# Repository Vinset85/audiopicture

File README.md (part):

# AudioPicture

Smart acoustic picture / complete Home Assistant room node.

**Product authority: [Rev.G frozen configuration](docs/architecture/v2.2-rev-g-clean.md).** 320 × 400 × 30 mm. Satellite1.1 Dev Kit and LD2450. One internal 24 V supply. Line-out to a stereo analog amplifier: XCITE XT19-4 on the left, Tectonic TEAX25C10-8/HS on the right. Volume is two taps on the bare bottom edge, left down and right up, with a latching microphone mute between them. Four LEDs sit under the cloth: white on header pin 1, blue on GPIO2 pin 13, red on GPIO14 pin 31, amber on GPIO18 pin 32. The 24-LED ring stays dark. The cloth drops into a front rabbet and finishes flush with the rim, held by fourteen magnets in that face. Frame: `mechanical/rev-g/cad/AP-G-FRAME.stl`. Digital checks: `evidence/rev-g/production-verification.json`. Not a production release.

**Supporting specs:** [DML panel](mechanical/dml-panel-rev-e.md), [electronics packaging](hardware/electronics-packaging-rev-e.md). Room logic already in `firmware/components/room_audio` and HA `room.py` carries forward; acoustic coefficients become DML-specific after measurement.

**Production package (digital):** [manufacturing/rev-e/](manufacturing/rev-e/) — gate register, BOM, OEM RFQ, assembly, factory test. CAD kernel STEP/STL in `mechanical/rev-e/cad/`. Modal screening in `evidence/rev-e/`. Mass production still requires OEM quotes, PCB fab, acoustic first article, product firmware on ESP-IDF, and certification (see gate register `OPEN_EXTERNAL`).

**Historical Rev.D (digital only, superseded):** [box model](mechanical/acoustic-box-model-rev-d.md) and [Rev.D architecture](docs/architecture/v2.2-rev-d-mono-room.md) for the 84 mm cone path.

**Historical structural checkpoint: [Rev.FI](mechanical/digital-validation-rev-fi.md).** It does not govern the radiator, the exciter, or the rear cavity. One serial refined-mesh weak-Y LC4 run passes the corner displacement check at 0.875290 mm and retains at least 0.173090 mm conservative final DML separation. The two-mesh displacement difference is 0.626581%; stress convergence remains OPEN. Weak-Z LC4 still fails. Materials, actual joints and complete product qualification remain OPEN. The 250 g frame ceiling remains removed.

The [Rev.FI supplement](https://github.com/Vinset85/audiopicture/releases/tag/checkpoint-rev-fi-2026-10-16) is published and verified: three attachments, 35 archive members (27 exact Git blobs and eight individually hashed raw artifacts). Receipts: [publication](evidence/rev-fi/github-publication.json), [archive consistency](evidence/rev-fi/archive-tree-verification.json).

A subsequent [Rev.FI stress-location audit](mechanical/lower-capture-hotspot-audit-rev-fi.md) locates unresolved peaks near the ideal lower capture and at the upper seal-collar junction. The available model cases transfer up to 47.609 N normal reaction through the ideal lower capture; this is not a measured capacity or a complete design-load envelope. The addendum is versioned in Git without altering the release archives.

The [Rev.FH supplement](https://github.com/Vinset85/audiopicture/releases/tag/checkpoint-rev-fh-2026-10-15) is published: all three asset names, sizes and SHA-256 digests match. Its 58 archive members match 43 Git blobs and 15 individually hashed raw artifacts. Receipts: [publication](evidence/rev-fh/github-publication.json) and [archive consistency](evidence/rev-fh/archive-tree-verification.json). Subsequent checks run one at a time, with audit and preservation before the next.

**Physical inputs needed:** [measurements, parameters and existing acceptance criteria](manufacturing/real-data-required-rev-fe.md). The [Rev.FG addendum](manufacturing/real-data-addendum-rev-fg.md) adds upper mounts, countersunk heads and seal-stack requirements. These plans separate coupon/component tests from first-assembly tests and the digital work still required.

## Project areas
- `hardware/` — electronics, BOM and KiCad design
- `mechanical/` — enclosure, DML panel and front-frame design
- `firmware/` — ESP32-S3 diagnostic implementation; production functions remain open
- `home-assistant/` — AudioPicture Home Assistant integration
- `manufacturing/` — factory provisioning and test
- `docs/` — architecture and engineering specifications

## Architecture baseline
**Rev.G** is the product authority. Earlier revisions stay in the tree as evidence.

See `docs/architecture/v2.2-rev-e-dml-30mm.md`, `docs/architecture/v2.2-rev-a.md`, and `hardware/bom/audiopicture-v2.2-rev-a.csv`.

## Digital validation checkpoint Rev.EN–EY

Rev.EM export/reimport is reproduced, but its labyrinth treatment fails:
only 4/22 vents have full chamber-footprint coverage, and 22/22 axial rays
are open. Fluid connectivity is not labyrinth treatment.

Rev.EQ is a verified geometric candidate with 22 stepped cells, not a
production freeze. Rev.ES corrects a conservative ESP32 RF-mask intrusion
in the frame kernel. Full-product structural/thermal, exact DMU/RF,
native electronics, material/process and physical qualification gates remain open.

See `mechanical/digital-validation-rev-en-es.md` and
`mechanical/test/physical-qualification-rev-er.json`.

Rev.EY adds real full-candidate frame screens, three mesh levels, 27 orthotropic
sensitivities, CG cases and buckling. EU.4 fails mass, torsion and
baffle clearance. EU.8, EU.9 and EU.10 recover mass/clearance but fail torsion; these
candidates are not fabrication-ready. Elmer natural-convection
benchmarks now converge and reproduce a published reference, but product CFD
is still OPEN. A portable power-governor core is host-tested; complete
ESP-IDF firmware, native electronics and Home Assistant remain OPEN.

## Checkpoint Rev.EZ — 2026-10-05

EU.11 recovers coarse geometry/mass/clearance but still fails the 1 mm LC4
criterion (1.544203 mm); no qualified frame is released. ENV native electrical
capture passes actual KiCad ERC and an independent pin-netlist check. Its
normal front optical path fails the DML geometric interference audit and PCB
integration remains open. Diagnostic ESP32-S3 firmware is actually compiled;
three host suites and 32 Home Assistant integration tests pass. Full product
firmware, all PCBs, native MAIN/VOICE/RADAR, qualified mechanics, full-product
CFD and physical qualification are still incomplete.

Evidence and remaining dependencies at that revision: `mechanical/digital-validation-rev-ez.md`
and `mechanical/validation/rev-ez/gate-register.json`.

## Checkpoint Rev.FA — 2026-10-06

A perimeter optical-island candidate clears the DML and a conservative +/-35
degree field of view. Carrier/coupon STEP reimport and STL integrity pass;
retention, interconnect, PCB split, baffle and physical calibration remain open.
EU.12 improves the LC1 normalized displacement to 1.337438 mm at 246.086 g
calculated mass, but still fails the LC4 corner limit: 1.455950 mm vs 1 mm.
Its executed nonlinear LC3 outward-pull screen also predicts DML interference
(20.933640 mm maximum displacement without DML contact). EU.12 is rejected
for assembly; improved vertical stiffness does not qualify the candidate.
No production CAD, qualified structural acceptance or product CFD is claimed.

Latest evidence and work still required:
`mechanical/digital-validation-rev-fa.md`,
`mechanical/optical-perimeter-candidate-rev-fa.md` and
`mechanical/validation/rev-fa/gate-register.json`.

## Checkpoint Rev.FB — 2026-10-07

Six actual LC1/LC3/LC4 runs compare EU.13 cruciform ribs and EU.14 intermediate
rail-to-perimeter ties. Both reduce LC3 displacement and show no sampled-node
DML interference; this does not qualify continuous deformed clearance. EU.13
fails mass (268.514 g), and both fail the 1 mm LC4 corner limit (1.412146 and
1.434103 mm). EU.14 mass is 249.525 g before unfinished interfaces. Neither
candidate is released for assembly. Registry: 38 PASS / 17 FAIL / 15 OPEN,
including historical and explicitly scoped diagnostic results.

See [Rev.FB report](mechanical/digital-validation-rev-fb.md),
[gate register](mechanical/validation/rev-fb/gate-register.json) and
[checkpoint publication policy](docs/validation-checkpoints.md).
The [complete Rev.FA baseline](https://github.com/Vinset85/audiopicture/releases/tag/checkpoint-rev-fa-2026-10-06)
is published: all 10 attachment sizes and SHA-256 digests match local files.
The [Rev.FB supplement](https://github.com/Vinset85/audiopicture/releases/tag/checkpoint-rev-fb-2026-10-07)
is also published: all 3 attachment sizes and SHA-256 digests are verified.
Receipts: `evidence/rev-fa/github-publication.json` and
`evidence/rev-fb/github-publication.json`.

## Checkpoint Rev.FC — 2026-10-07

Four new CAD candidates and five actual CalculiX runs are consolidated.
EU.18 weighs 249.328 g at catalog density but fails LC4 on both meshes:
1.389561 mm / 1.392602 mm versus 1 mm; the displacement difference is 0.218%.
LC1 is 7.179289 mm and LC3 is 8.952446 mm maximum normalized displacement.
No sampled LC3 node enters the DML; continuous deformed clearance is open.
EU.15 fails mass and torsion, EU.16 is CAD-only, EU.17 meshing failed twice.
No candidate is released for assembly. Registry: 47 PASS / 23 FAIL / 17 OPEN,
including historical and scoped diagnostics, not a completion percentage.

The 250 g frame target originated as a system mass allocation, excluding
inserts and metal cleats; it is not a material limit. The historical 1.55 kg
system budget is stale. Mass must be reviewed together with stiffness and
complete-assembly CAD; no new target or assembled mass is released.

See [Rev.FC results](mechanical/digital-validation-rev-fc.md),
[mass-budget review](mechanical/system-mass-review-rev-fc.md),
[gate register](mechanical/validation/rev-fc/gate-register.json) and
[publication status](docs/validation-checkpoints.md).

The [Rev.FC supplement](https://github.com/Vinset85/audiopicture/releases/tag/checkpoint-rev-fc-2026-10-07)
is published: all three asset sizes and SHA-256 digests are verified against
GitHub. Receipt: `evidence/rev-fc/github-publication.json`.

## Checkpoint Rev.FD — 2026-10-08

The [mass policy](mechanical/mass-policy-rev-fd.md) removes the 250 g rejection
gate without inventing a replacement ceiling. Mass/CG and load adequacy remain
tracked; 70 N is the minimum vertical seed, with actual additional 90 N screens.

Two CAD candidates, four meshes and 13 new CalculiX runs are verified. EU.19
weighs 442.655 g at catalog density and still fails LC4: 1.006463 / 1.004060 mm.
EU.20 weighs 456.315 g and passes the normalized four-corner 30 N displacement
screen: LR 0.953041, LL 0.955552, UL 0.163397, UR 0.166741 mm. Fine-mesh LR is
0.957329 mm, a 0.448% two-mesh change. This does not qualify stress, real mounts,
material/process, full LC1–LC7 sensitivity/buckling, or production readiness.

EU.20 LC1 maxima are 2.314278 mm at 70 N and 2.975500 mm at 90 N; nonlinear
LC3 outward-pull maximum is 2.049186 mm. A conservative Bernstein enclosure
checks every full quadratic FEA element against the fixed DML box at final
LC3 load: no overlapping bounds, at least 0.324156 mm modeled separation.
Exact deformed CAD, tolerances and physical assembly clearance remain open.

Registry including history: 64 PASS / 25 FAIL / 18 OPEN. Eight historical
mass-only gates are explicitly superseded; counts are not completion percentages.
See the [report](mechanical/digital-validation-rev-fd.md),
[register](mechanical/validation/rev-fd/gate-register.json), and
[publication record](docs/validation-checkpoints.md).

The [Rev.FD supplement](https://github.com/Vinset85/audiopicture/releases/tag/checkpoint-rev-fd-2026-10-08)
is published on commit `26b60bea5645258ce13141e7a85896333513810b`.
All three attachment names, sizes and SHA-256 digests are verified against
GitHub. Receipt: `evidence/rev-fd/github-publication.json`.

## Checkpoint Rev.FE — 2026-10-09

14 full-frame runs and 18 independent material-axis checks are actually executed.
The weaker normalized material makes EU.20/EU.21/EU.22 fail the flat-print
LC4 criterion; EU.22 remains above 1 mm on both meshes despite 605.105 g
calculated mass. EU.20 weak-Y orientation gives 0.825603/0.826344 mm at the
two lower corners, but linear vertical screens predict DML interference.
The separate contact/nonlinear 100 N run also fails refined full-element DML clearance, with 57 intersecting sampled nodes and additional interior-element witnesses. Its limitations are in the report.
No production orientation, strength or complete FEA matrix is qualified.

ASA sidewalls preserve all 22 rear labyrinth cells, while a BREP path audit
proves three unmanaged front-joint paths. An original ruthex M4 CAD and a
catalog-sized installation coupon are verified; the provisional frame bores
are incompatible with that insert specification. Actual seals, mounts,
full-product CFD, electronics/PCB, functional firmware and physical qualification
remain incomplete. See [Rev.FE results](mechanical/digital-validation-rev-fe.md)
and [required real measurements](manufacturing/real-data-required-rev-fe.md).
Registry including history: 78 PASS / 39 FAIL / 21 OPEN.
The [Rev.FE supplement](https://github.com/Vinset85/audiopicture/releases/tag/checkpoint-rev-fe-2026-10-09)
was published on 11 October on commit `3996b697d6673c8ac19a297206d947c2e36917c9`.
All three attachment names, sizes and SHA-256 digests match GitHub; the tag
commit is verified. All 218 versioned files in the archive match that
engineering commit; 178 raw artifacts are individually SHA-256 checked.
Receipts: `evidence/rev-fe/github-publication.json` and
`evidence/rev-fe/archive-tree-verification.json`. Publication integrity does
not qualify the design for production.

## Checkpoint Rev.FG — 2026-10-14

The upper assembly now has recessed cleats, catalog-sized M4 bores and
countersunk screw envelopes. Reimported CAD passes 187 coarse keepout checks,
continuous 7 mm lift/extraction checks and capped-air partition controls;
removing each of four mounting seals reconnects its pocket to the rear cavity.
The existing 22 labyrinth cells are geometrically preserved. Nominal seals
and rigid motion do not qualify leakage, tolerances or actual contact strength.

Four full-frame CalculiX runs are executed on three successive geometries.
On the current 468.724 g frame (calculated at catalog density), nonlinear
LC1 100 N weak-Y retains at least 0.823384 mm modeled DML separation.
LC4 weak-Z reaches 1.141787 mm against a 1 mm limit and has 19 robust
interior-element DML interference witnesses: FAIL. No production release.

The gasket stack calculation exposes tight conditional gap budgets. A fixed
DML retainer, adjustable stops, lower capture, full contact/orthotropic FEA,
product CFD and complete electronics/firmware remain digital work to finish.
All physical tests remain NOT_RUN. The prior FE zero-node claim is corrected:
the EU20 LC1 100 N weak-Y nonlinear case had 57 intersecting sampled nodes.

See [Rev.FG report](mechanical/digital-validation-rev-fg.md),
[gate register](mechanical/validation/rev-fg/gate-register.json),
[component candidates](mechanical/components/upper-mount-candidates-rev-fg.json)
and [physical-test addendum](manufacturing/real-data-addendum-rev-fg.md).

The [Rev.FG supplement](https://github.com/Vinset85/audiopicture/releases/tag/checkpoint-rev-fg-2026-10-14)
is published on 15 October at commit `d2dbe81e34abad0a0a7c749e5e940226d7e55684`.
All three asset names, sizes and SHA-256 digests match GitHub. The archive
contains 115 files matching their Git blobs and 86 raw artifacts checked
individually. Receipts: `evidence/rev-fg/github-publication.json` and
`evidence/rev-fg/archive-tree-verification.json`. The prior Rev.FE release
description is corrected while its three original assets remain unchanged.

## Current checkpoint Rev.FH — 2026-10-15

Three completed nonlinear weak-Y screens use the unchanged FG frame and M0
mesh. Lower-corner LC4 reaches 0.869805 / 0.870653 mm against 1 mm, with
conservative full-element DML separation of at least 0.177358 / 0.176540 mm.
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
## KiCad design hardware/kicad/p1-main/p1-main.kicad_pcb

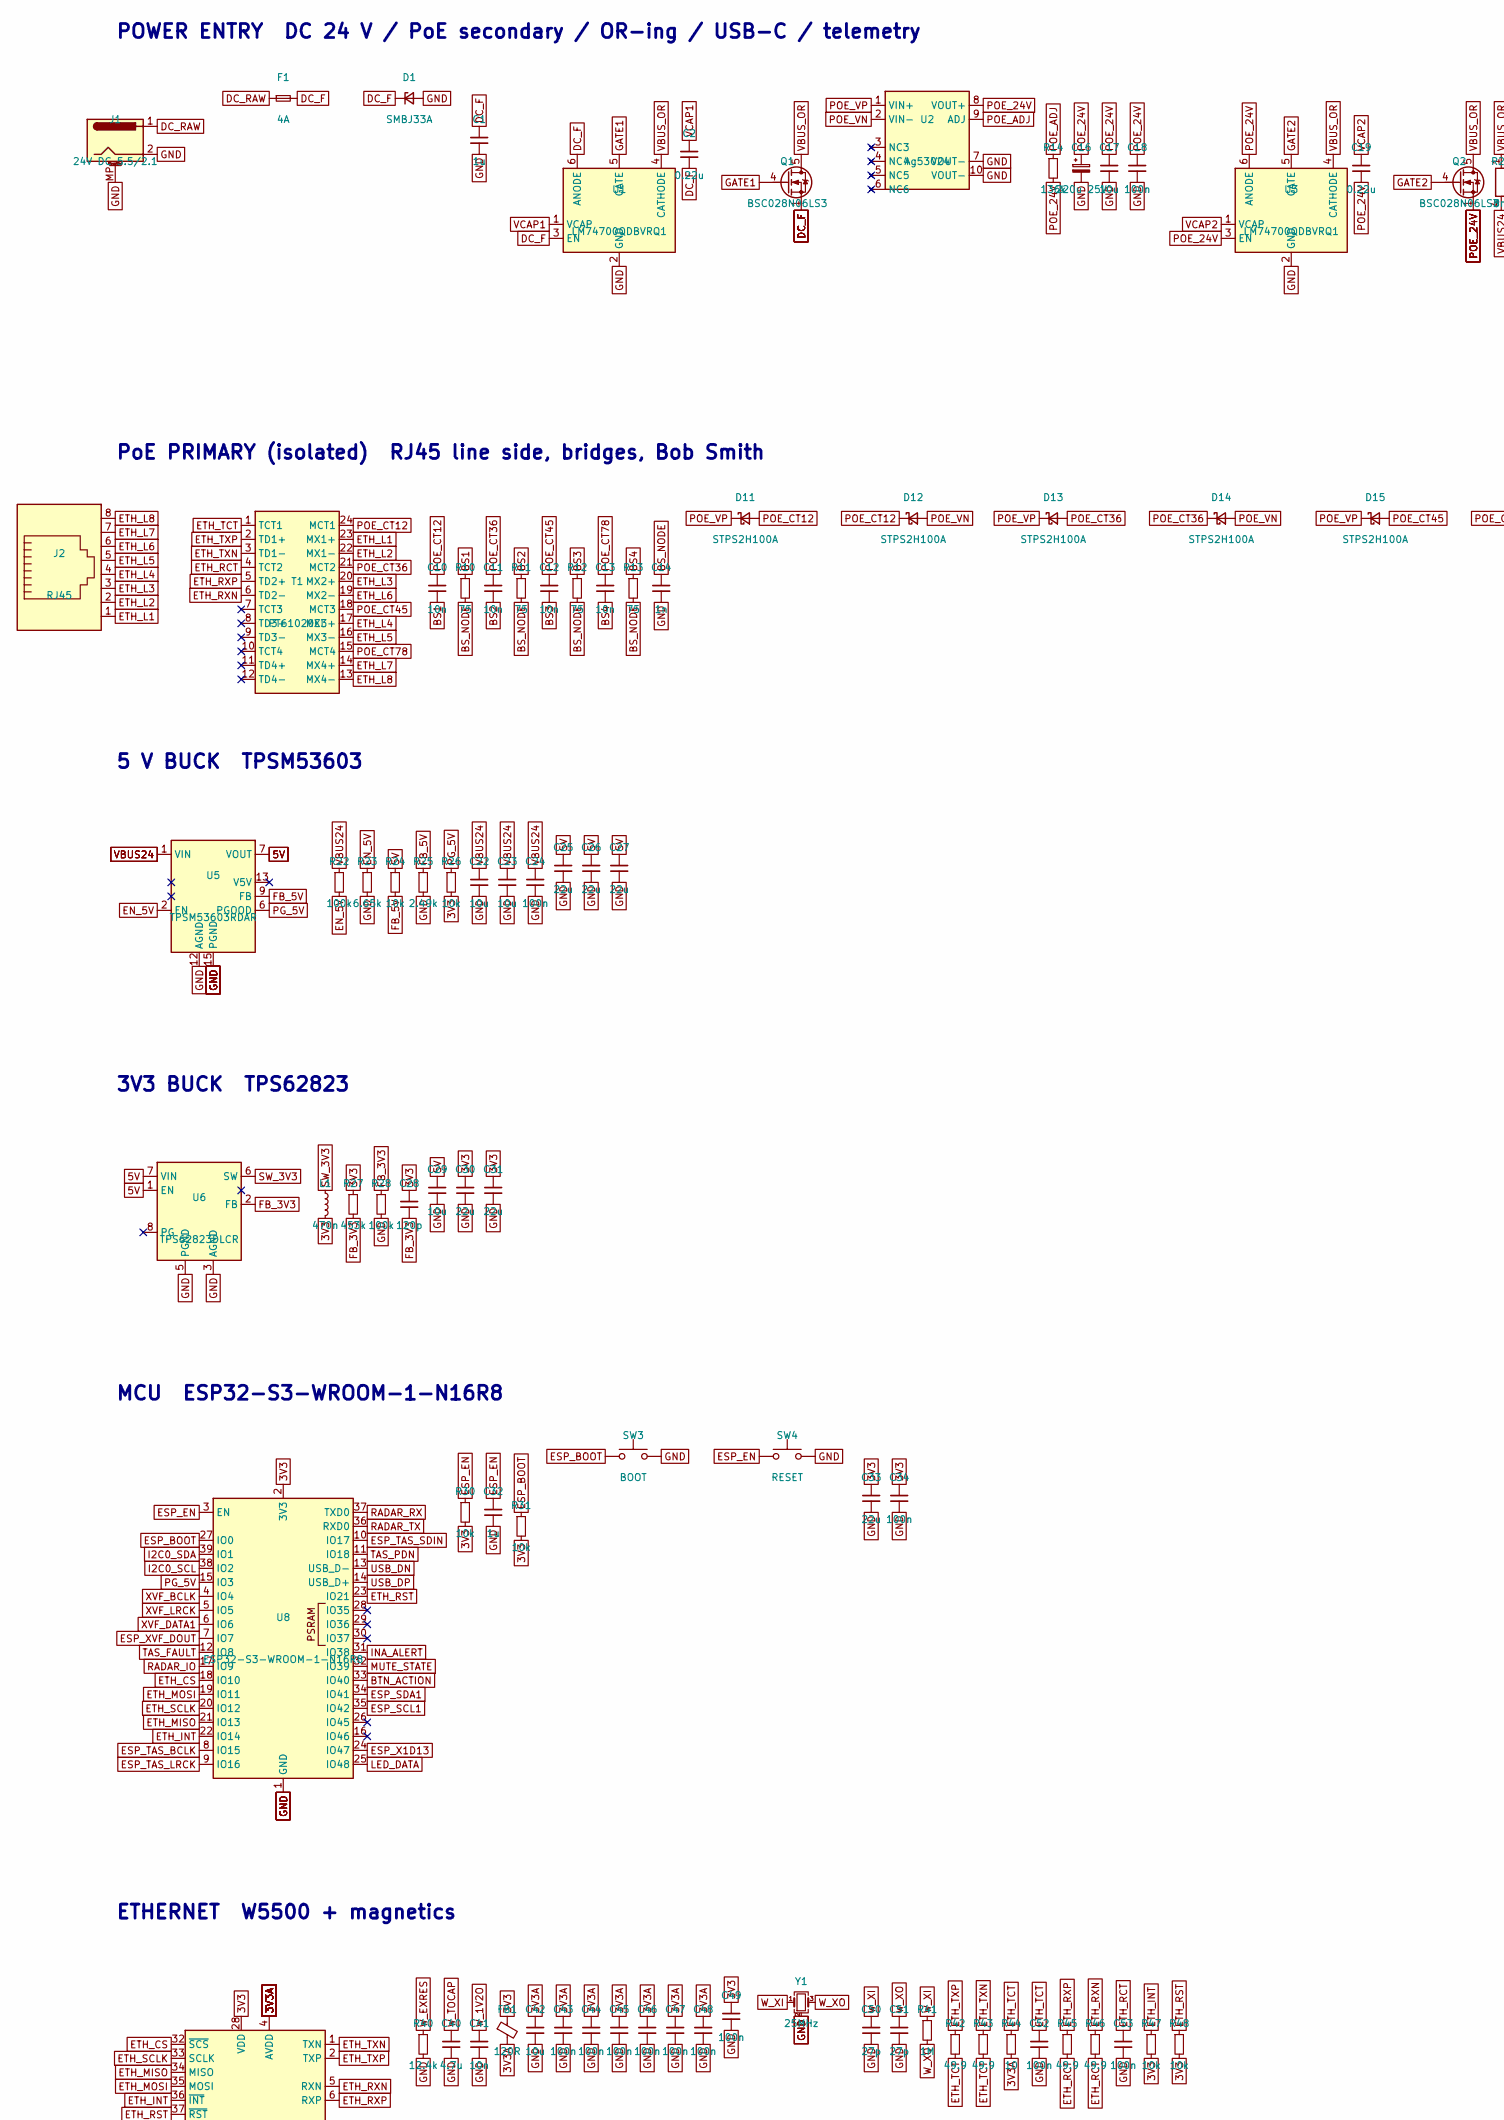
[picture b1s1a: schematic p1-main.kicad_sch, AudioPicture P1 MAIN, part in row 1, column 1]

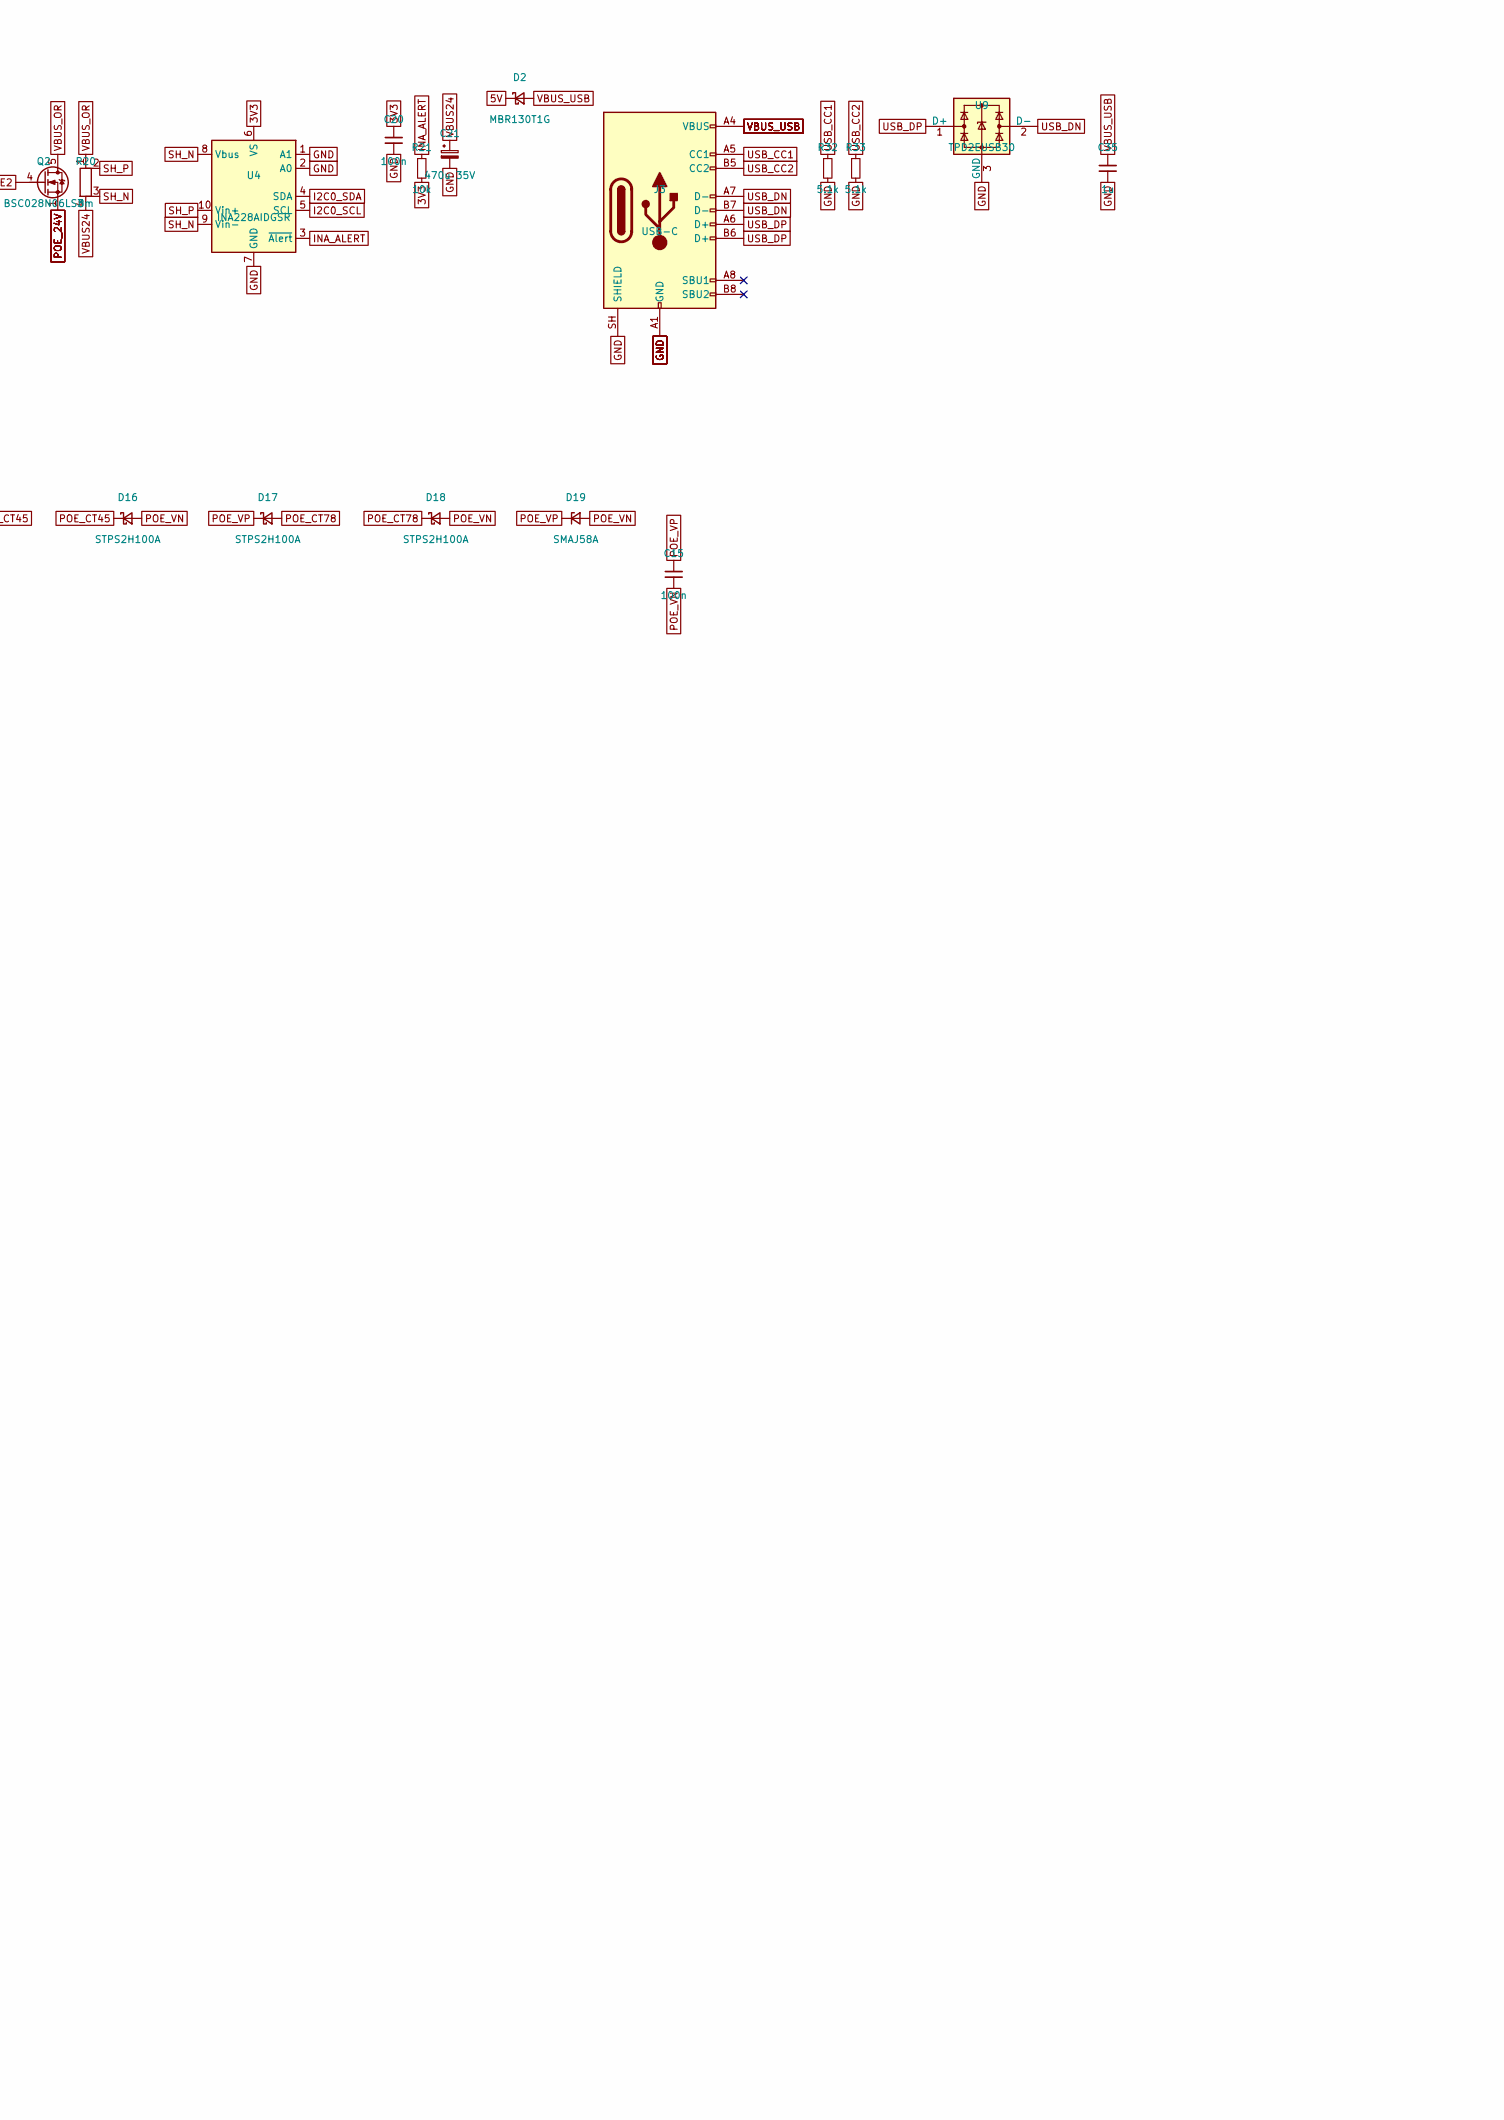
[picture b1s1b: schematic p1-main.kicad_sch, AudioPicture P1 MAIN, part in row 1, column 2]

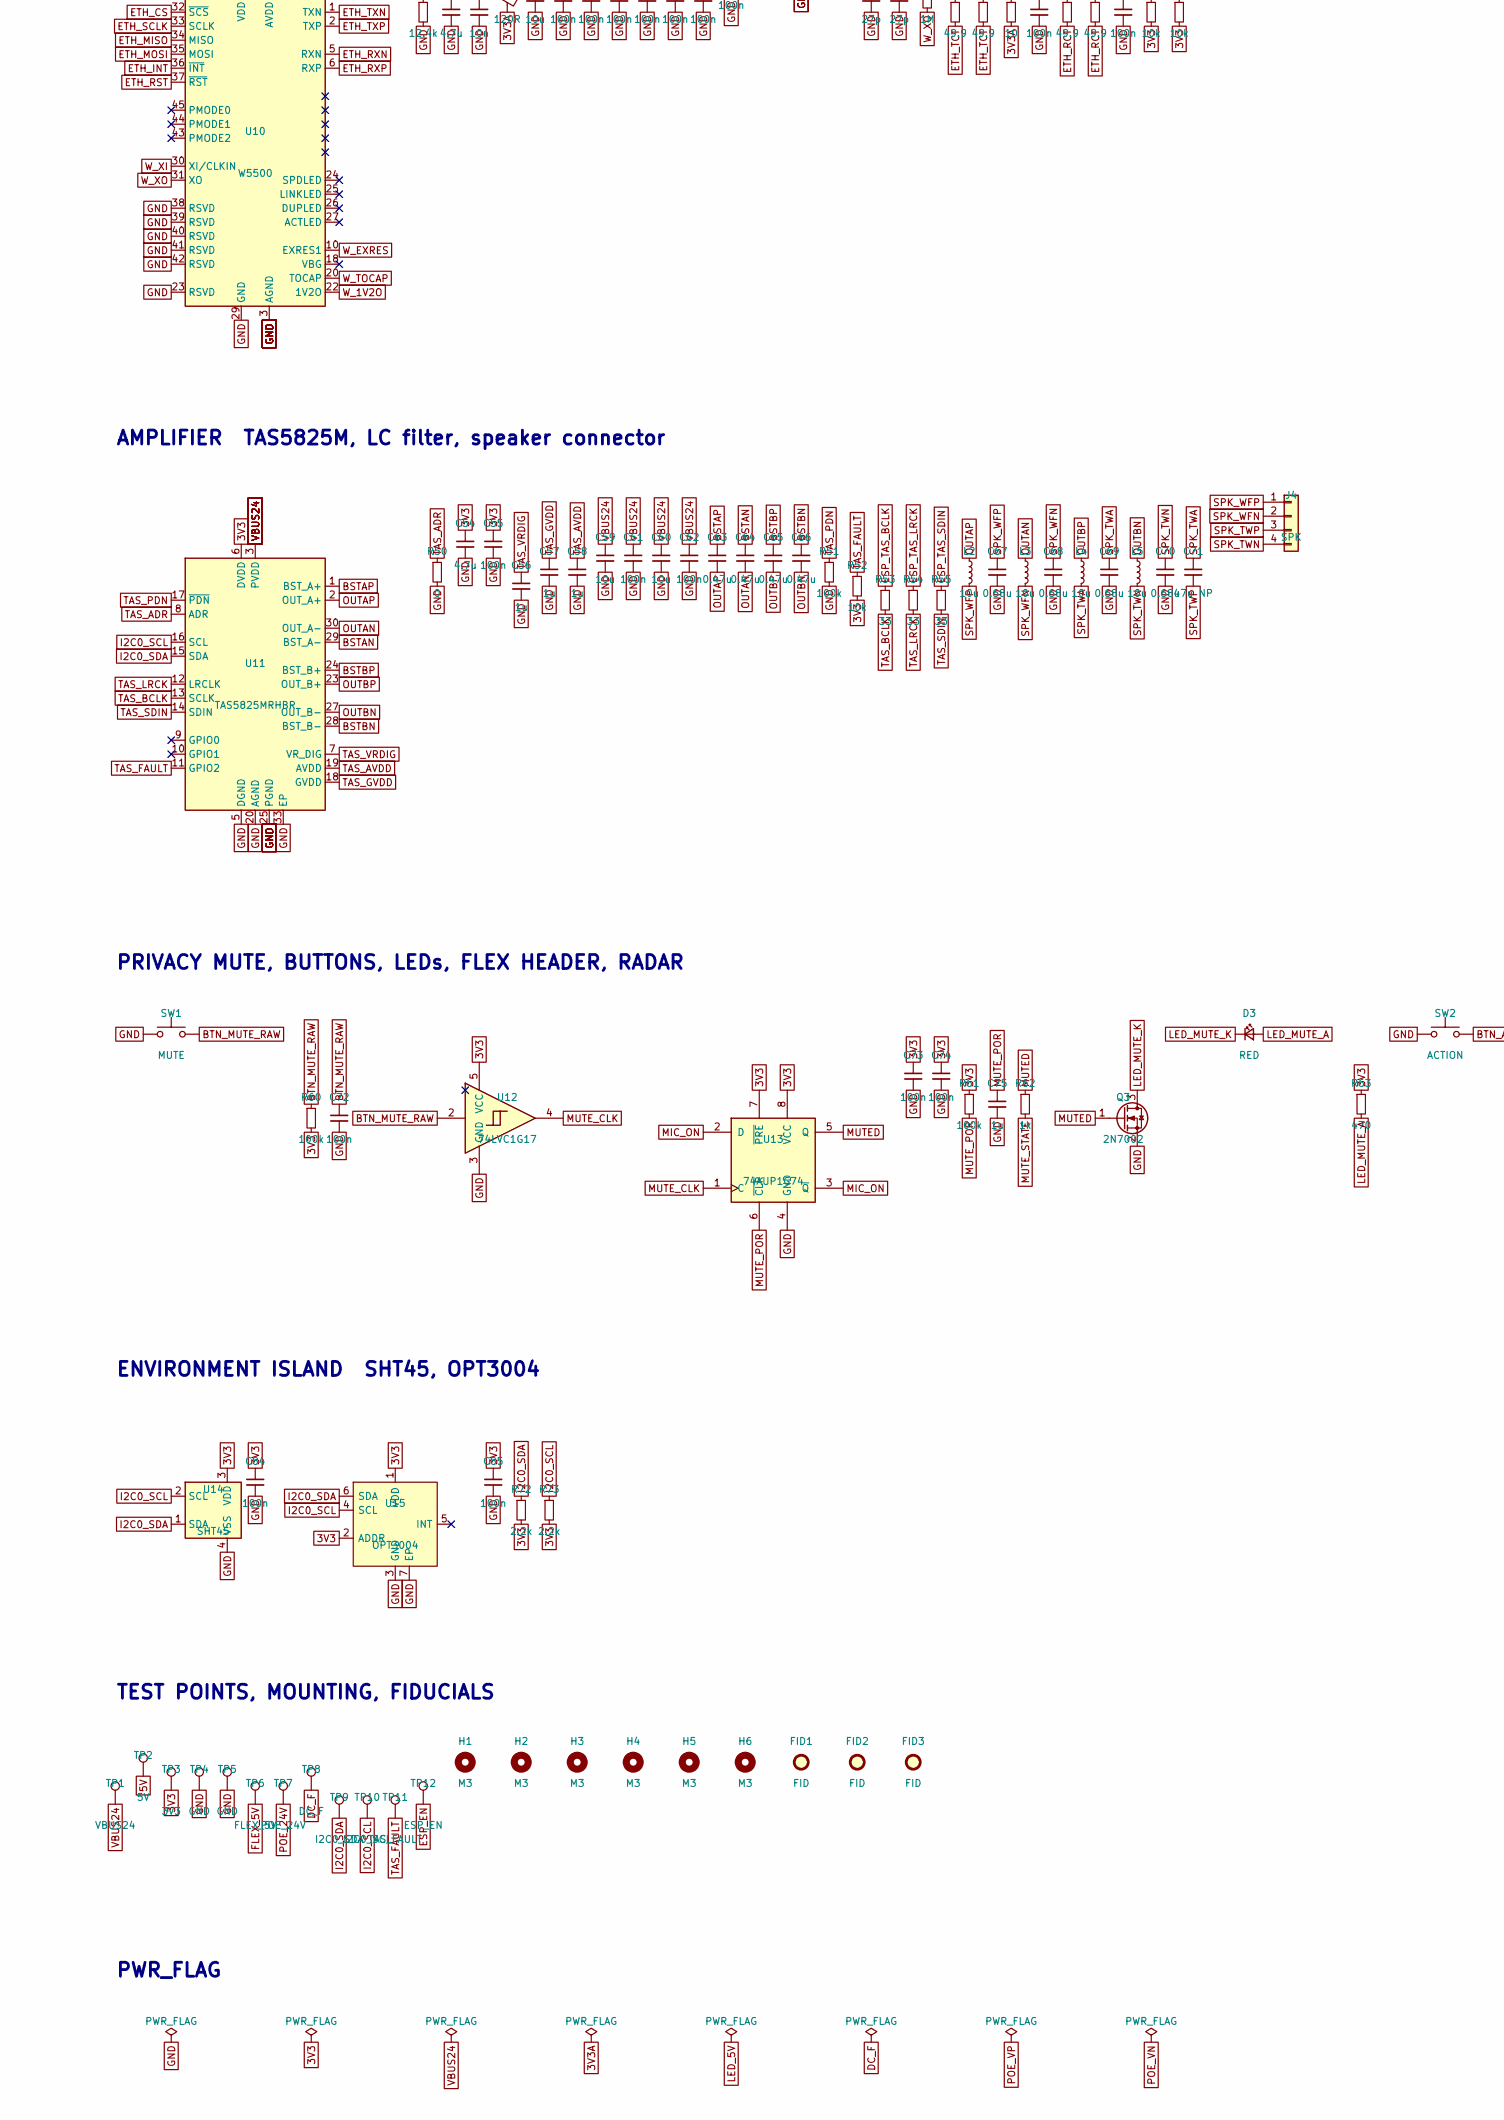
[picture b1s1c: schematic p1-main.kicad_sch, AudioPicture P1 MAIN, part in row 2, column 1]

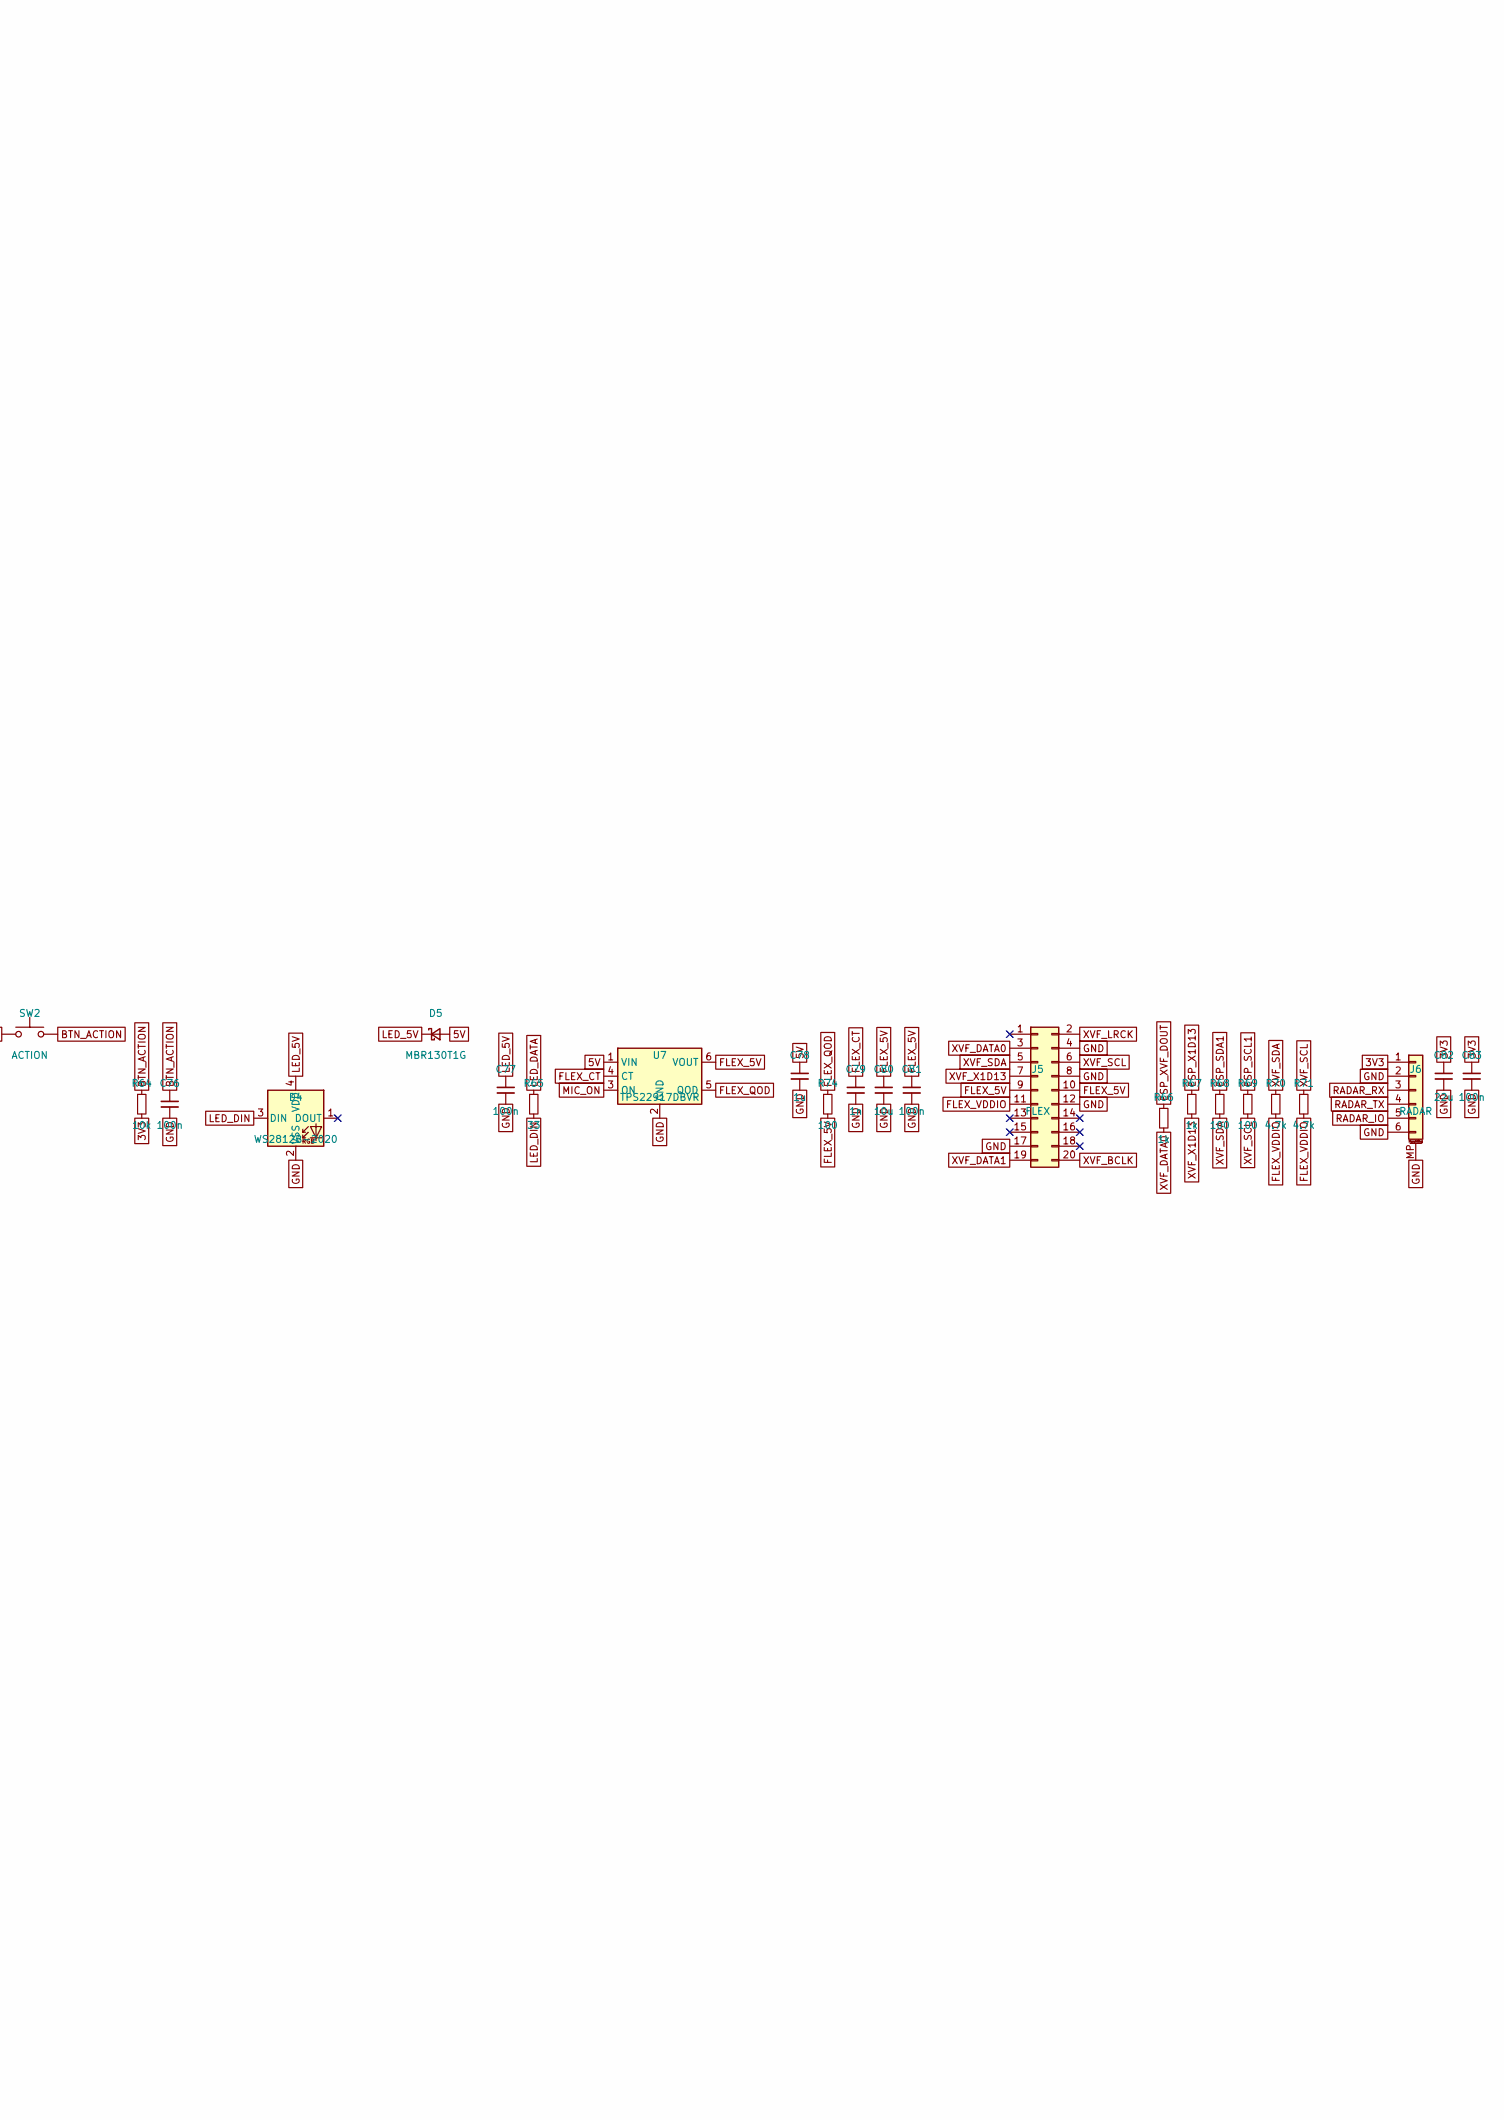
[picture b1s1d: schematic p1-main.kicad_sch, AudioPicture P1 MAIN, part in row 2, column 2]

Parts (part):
C1: 1u; C_0805_2012Metric; MPN Murata GRM21BR71H105KA12L
C2, C19: 0.22u; C_0603_1608Metric; MPN Murata GRM188R71E224KA88D
C10, C11, C12, C13: 10n; C_0603_1608Metric; MPN Murata GRM188R72A103KA01D
C14: 1n; C_1808_4520Metric; MPN Vishay VJ1808Y102KXGAT
C15: 100n; C_0805_2012Metric; MPN Murata GRM21BR72A104KAC4L
C16: 220u 25V; CP_Elec_8x10.5; MPN Panasonic EEE-FK1E221P
C17, C59, C60: 10u; C_1210_3225Metric; MPN TDK C3225X7R1H106M250AC
C18, C24: 100n; C_0603_1608Metric; MPN Murata GRM188R71H104KA93D
C20, C34, C43, C44, C45, C46, C47, C48, C49, C52, C53, C55, C72, C73, C74, C76, C77, C81, C83, C84, C85: 100n; C_0402_1005Metric; MPN Murata GRM155R71C104KA88D
C21: 470u 35V; CP_Radial_D10.0mm_P5.00mm; MPN Panasonic EEU-FR1V471B
C22, C23: 10u; C_1206_3216Metric; MPN TDK C3216X5R1H106K160AB
C25, C26, C27: 22u; C_1210_3225Metric; MPN TDK C3225X7R1E226M250AB
C28: 120p; C_0402_1005Metric; MPN Murata GRM1555C1H121JA01D
C29, C42, C80: 10u; C_0805_2012Metric; MPN Murata GRM21BR71A106KA73L
C30, C31, C33, C82: 22u; C_0805_2012Metric; MPN Murata GRM21BR61A226ME44L
C32, C35, C56, C57, C58, C75, C78: 1u; C_0603_1608Metric; MPN Murata GRM188R71E105KA12D
C40, C54: 4.7u; C_0603_1608Metric; MPN Murata GRM188R61A475KE15D
C41: 10n; C_0402_1005Metric; MPN Murata GRM155R71H103KA88D
C50, C51: 27p; C_0402_1005Metric; MPN Murata GRM1555C1H270JA01D
C61, C62: 100n; C_0402_1005Metric; MPN Murata GRM155R71H104KE14D
C63, C64, C65, C66: 0.47u; C_0603_1608Metric; MPN Murata GRM188R71E474KA12D
C67, C68, C69, C70: 0.68u; C_0805_2012Metric; MPN Murata GRM21BR71H684KA88L
C71: 47u NP; C_Radial_D10.0mm_H12.5mm_P5.00mm; MPN Nichicon UES1H470MPM
C79: 1n; C_0402_1005Metric; MPN Murata GRM155R71H102KA01D
D1: SMBJ33A; D_SMB; MPN Littelfuse SMBJ33A
D2, D5: MBR130T1G; D_SOD-123; MPN onsemi MBR130T1G
D3: RED; LED_0603_1608Metric; MPN Kingbright APT1608EC
D4: WS2812B-2020; LED_WS2812B-2020_PLCC4_2.0x2.0mm; MPN Worldsemi WS2812B-2020
D11, D12, D13, D14, D15, D16, D17, D18: STPS2H100A; D_SMA; MPN ST STPS2H100A
D19: SMAJ58A; D_SMA; MPN Littelfuse SMAJ58A
F1: 4A; Fuse_Littelfuse-NANO2-451_453; MPN Littelfuse 0453004.MR
FB1: 120R; L_0603_1608Metric; MPN Murata BLM18PG121SN1D
FID1, FID2, FID3: FID; Fiducial_1mm_Mask2mm
H1, H2, H3, H4, H5, H6: M3; MountingHole_3.2mm_M3
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
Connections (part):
3V3: C20.1, C28.1, C30.1, C31.1, C33.1, C34.1, C49.1, C54.1, C55.1, C73.1, C74.1, C82.1, C83.1, C84.1, C85.1, FB1.1, J6.1, L1.2, R21.2, R26.2, R27.1, R30.2, R31.2, R47.2, R48.2, R52.2, R60.2, R61.1, R63.1, R64.2, R72.2, R73.2, TP3.1, U4.6 (VS), U8.2 (3V3), U10.28 (VDD), U11.6 (DVDD), U12.5 (VCC), U13.7 (~PRE), U13.8 (VCC), U14.3 (VDD), U15.1 (VDD), U15.2 (ADDR)
3V3A: C42.1, C43.1, C44.1, C45.1, C46.1, C47.1, C48.1, FB1.2, R44.2, U10.4 (AVDD), U10.8 (AVDD), U10.11 (AVDD), U10.15 (AVDD), U10.17 (AVDD), U10.21 (AVDD)
5V: C25.1, C26.1, C27.1, C29.1, C78.1, D2.1 (K), D5.2 (A), R24.1, TP2.1, U5.7 (VOUT), U5.8 (VOUT), U6.1 (EN), U6.7 (VIN), U7.1 (VIN)
BS1: C10.2, R10.1
BS2: C11.2, R11.1
BS3: C12.2, R12.1
BS4: C13.2, R13.1
BSTAN: C64.1, U11.29 (BST_A-)
BSTAP: C63.1, U11.1 (BST_A+)
BSTBN: C66.1, U11.28 (BST_B-)
BSTBP: C65.1, U11.24 (BST_B+)
BS_NODE: C14.1, R10.2, R11.2, R12.2, R13.2
BTN_ACTION: C76.1, R64.1, SW2.2, U8.33 (IO40)
BTN_MUTE_RAW: C72.1, R60.1, SW1.2, U12.2
DC_F: C1.1, C2.2, D1.1 (K), F1.2, Q1.1 (S), Q1.2 (S), Q1.3 (S), TP8.1, U1.3 (EN), U1.6 (ANODE)
DC_RAW: F1.1, J1.1
EN_5V: R22.2, R23.1, U5.2 (EN)
ESP_BOOT: R31.1, SW3.1, U8.27 (IO0)
ESP_EN: C32.1, R30.1, SW4.1, TP12.1, U8.3 (EN)
ESP_SCL1: R69.1, U8.35 (IO42)
ESP_SDA1: R68.1, U8.34 (IO41)
ESP_TAS_BCLK: R53.1, U8.8 (IO15)
ESP_TAS_LRCK: R54.1, U8.9 (IO16)
ESP_TAS_SDIN: R55.1, U8.10 (IO17)
ESP_X1D13: R67.1, U8.24 (IO47)
ESP_XVF_DOUT: R66.1, U8.7 (IO7)
ETH_CS: U8.18 (IO10), U10.32 (~SCS)
ETH_INT: R47.1, U8.22 (IO14), U10.36 (~INT)
ETH_L1: J2.1, T1.23 (MX1+)
ETH_L2: J2.2, T1.22 (MX1-)
ETH_L3: J2.3, T1.20 (MX2+)
ETH_L4: J2.4, T1.17 (MX3+)
ETH_L5: J2.5, T1.16 (MX3-)
ETH_L6: J2.6, T1.19 (MX2-)
ETH_L7: J2.7, T1.14 (MX4+)
ETH_L8: J2.8, T1.13 (MX4-)
ETH_MISO: U8.21 (IO13), U10.34 (MISO)
ETH_MOSI: U8.19 (IO11), U10.35 (MOSI)
ETH_RCT: C53.1, R45.2, R46.2, T1.4 (TCT2)
ETH_RST: R48.1, U8.23 (IO21), U10.37 (~RST)
ETH_RXN: R46.1, T1.6 (TD2-), U10.5 (RXN)
ETH_RXP: R45.1, T1.5 (TD2+), U10.6 (RXP)
ETH_SCLK: U8.20 (IO12), U10.33 (SCLK)
ETH_TCT: C52.1, R42.2, R43.2, R44.1, T1.1 (TCT1)
ETH_TXN: R43.1, T1.3 (TD1-), U10.1 (TXN)
ETH_TXP: R42.1, T1.2 (TD1+), U10.2 (TXP)
FB_3V3: C28.2, R27.2, R28.1, U6.2 (FB)
FB_5V: R24.2, R25.1, U5.9 (FB)
FLEX_5V: C80.1, C81.1, J5.9, J5.10, R74.2, TP6.1, U7.6 (VOUT)
FLEX_CT: C79.1, U7.4 (CT)
FLEX_QOD: R74.1, U7.5 (QOD)
FLEX_VDDIO: J5.11, R70.2, R71.2
GATE1: Q1.4 (G), U1.5 (GATE)
GATE2: Q2.4 (G), U3.5 (GATE)
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
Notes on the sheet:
POWER ENTRY DC 24 V / PoE secondary / OR-ing / USB-C / telemetry
PoE PRIMARY (isolated) RJ45 line side, bridges, Bob Smith
5 V BUCK TPSM53603
3V3 BUCK TPS62823
MCU ESP32-S3-WROOM-1-N16R8
ETHERNET W5500 + magnetics
AMPLIFIER TAS5825M, LC filter, speaker connector
PRIVACY MUTE, BUTTONS, LEDs, FLEX HEADER, RADAR
ENVIRONMENT ISLAND SHT45, OPT3004
TEST POINTS, MOUNTING, FIDUCIALS
PWR_FLAG

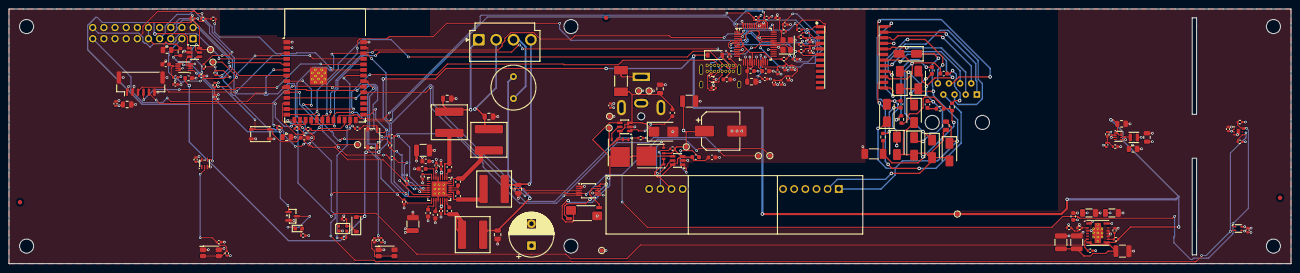
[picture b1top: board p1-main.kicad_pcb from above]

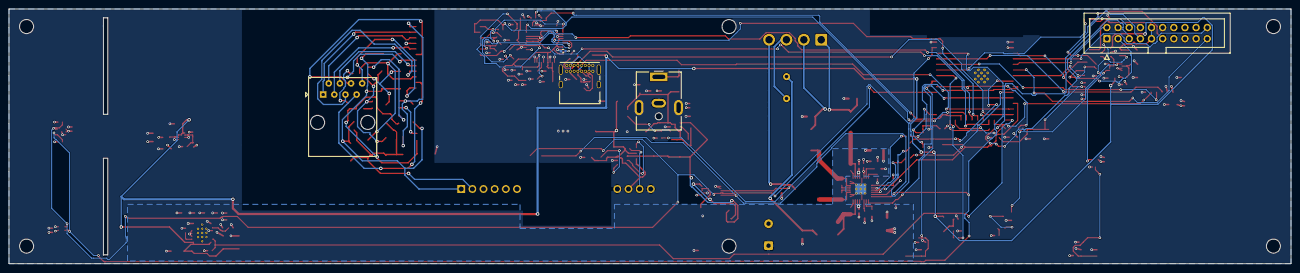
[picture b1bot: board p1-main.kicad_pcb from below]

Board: 4 copper layers, 292.0 x 58.0 mm, 194 parts (5 on the bottom side), 122 nets.

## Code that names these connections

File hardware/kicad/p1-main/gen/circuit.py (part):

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     note="mating face toward -Y, plug inserted from the bay floor")
part("F1", "Device:Fuse_Small", "4A", "Fuse:Fuse_Littelfuse-NANO2-451_453", {"1": "DC_RAW", "2": "DC_F"},
     "Littelfuse 0453004.MR", "PIN")
part("D1", "Device:D_Zener_Small", "SMBJ33A", "Diode_SMD:D_SMB", {"1": "DC_F", "2": "GND"}, "Littelfuse SMBJ33A", "PIN",
     note="unidirectional TVS, cathode (pad 1, band) on DC_F")
C("C1", "1u", "DC_F", "GND", "PIN", key="1u50", size="0805")
part("U1", "Power_Management:LM74700", "LM74700QDBVRQ1", "Package_TO_SOT_SMD:SOT-23-6",
     {"1": "VCAP1", "2": "GND", "3": "DC_F", "4": "VBUS_OR", "5": "GATE1", "6": "DC_F"}, "TI LM74700QDBVRQ1", "PIN")
C("C2", "0.22u", "VCAP1", "DC_F", "PIN", key="0u22", size="0603")
part("Q1", "Transistor_FET:BSC028N06LS3", "BSC028N06LS3", "Package_TO_SOT_SMD:TDSON-8-1",
     {"1": "DC_F", "2": "DC_F", "3": "DC_F", "4": "GATE1", "5": "VBUS_OR"}, "Infineon BSC028N06LS3GATMA1", "PIN")

# ======================================================================== POWER ENTRY: PoE (primary side)
part("J2", "Connector:RJ45", "RJ45", "Connector_RJ:RJ45_Amphenol_54602-x08_Horizontal",
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     {"1": "POE_VP", "2": "POE_VN", "7": "GND", "8": "POE_24V", "9": "POE_ADJ", "10": "GND"},
     "Silvertel Ag53024", at=(203.0, 33.0), rot=180.0, h=18.0,
     note="pin 1 at (203,33); module body toward -Y; primary pins 1-6 right, secondary 7-10 left")
R("R14", "136k", "POE_ADJ", "POE_24V", "PIN", note="lowers VOUT to ~22.8 V so the DC input wins the OR (VERIFY Ag53000 ADJ table)")
part("C16", "Device:C_Polarized_Small", "220u 25V", "Capacitor_SMD:CP_Elec_8x10.5", {"1": "POE_24V", "2": "GND"},
     "Panasonic EEE-FK1E221P", "PIN", h=10.5)
C("C17", "10u", "POE_24V", "GND", "PIN", key="10u50", size="1210")
C("C18", "100n", "POE_24V", "GND", "PIN", key="100n50", size="0603")
part("U3", "Power_Management:LM74700", "LM74700QDBVRQ1", "Package_TO_SOT_SMD:SOT-23-6",
     {"1": "VCAP2", "2": "GND", "3": "POE_24V", "4": "VBUS_OR", "5": "GATE2", "6": "POE_24V"}, "TI LM74700QDBVRQ1", "PIN")
C("C19", "0.22u", "VCAP2", "POE_24V", "PIN", key="0u22", size="0603")
part("Q2", "Transistor_FET:BSC028N06LS3", "BSC028N06LS3", "Package_TO_SOT_SMD:TDSON-8-1",
     {"1": "POE_24V", "2": "POE_24V", "3": "POE_24V", "4": "GATE2", "5": "VBUS_OR"}, "Infineon BSC028N06LS3GATMA1", "PIN")

# ======================================================================== measurement and bus
part("R20", "Device:R_Shunt", "8m", "Resistor_SMD:R_Shunt_Vishay_WSK2512_6332Metric_T1.19mm",
     {"1": "VBUS_OR", "2": "SH_P", "3": "SH_N", "4": "VBUS24"}, "Vishay WSK25128L000FEA", "PIN")
part("U4", "Sensor_Energy:INA228", "INA228AIDGSR", "Package_SO:TSSOP-10_3x3mm_P0.5mm",
     {"1": "GND", "2": "GND", "3": "INA_ALERT", "4": "I2C0_SDA", "5": "I2C0_SCL", "6": "3V3", "7": "GND",
      "8": "SH_N", "9": "SH_N", "10": "SH_P"}, "TI INA228AIDGSR", "PIN", note="I2C 0x40")
C("C20", "100n", "3V3", "GND", "PIN")
R("R21", "10k", "INA_ALERT", "3V3", "PIN")
part("C21", "Device:C_Polarized_Small", "470u 35V", "Capacitor_THT:CP_Radial_D10.0mm_P5.00mm",
     {"1": "VBUS24", "2": "GND"}, "Panasonic EEU-FR1V471B", at=(128.0, 22.0), rot=90.0, h=16.0,
     note="PVDD bulk; 10 x 16 mm (VERIFY height vs 16.5 envelope)")
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     {"A1": "GND", "A12": "GND", "B1": "GND", "B12": "GND", "A4": "VBUS_USB", "A9": "VBUS_USB", "B4": "VBUS_USB",
      "B9": "VBUS_USB", "A5": "USB_CC1", "B5": "USB_CC2", "A6": "USB_DP", "B6": "USB_DP", "A7": "USB_DN", "B7": "USB_DN",
      "SH": "GND"}, "GCT USB4085-GF-A", at=(176.0, 52.0), side="B", rot=0, h=3.3)
R("R32", "5.1k", "USB_CC1", "GND", "PIN")
R("R33", "5.1k", "USB_CC2", "GND", "PIN")
part("U9", "Power_Protection:TPD2EUSB30", "TPD2EUSB30", "Package_TO_SOT_SMD:Texas_DRT-3",
     {"1": "USB_DP", "2": "USB_DN", "3": "GND"}, "TI TPD2EUSB30DRTR", "PIN")
C("C35", "1u", "VBUS_USB", "GND", "PIN", size="0603")

# ======================================================================== Ethernet W5500
part("U10", "Interface_Ethernet:W5500", "W5500", "Package_QFP:LQFP-48_7x7mm_P0.5mm",
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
